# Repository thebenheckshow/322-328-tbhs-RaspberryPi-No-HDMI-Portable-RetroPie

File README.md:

# 322-328-tbhs-RaspberryPi-No-HDMI-Portable-RetroPie
We direct drive a TFT screen with the GPIO of a Rarspberry Pi, connect a GPIO button matrix, install RetroPie, and put it in a sleek portable game form factor.

General overview of steps:

What we did was download and install RetroPie.
Then we connected a TFT screen throught an adapter board from Adafruit.
We used 5 6 5 for the color bit depth. That is 5 bits red 6 bits green and 5 bits blue.
After connecting the screen we made a custom device tree overlay to drive the TFT screen via the GPIO connection.

Using 5 6 5 color bit depth for the TFT screen left us with exactly 8 GPIO for input.
We created a 4x4 button matrix and connected it to the GPIO.
In order to get the operating system to take input from the GPIO button matrix we needed to recompile the kernel with the GPIO button matrix kernel module enabled.
Next we created another device tree overlay to drive the GPIO button matrix.

With all the software and hardware working, Mr. Heckendorn created a sleek enclosure with a nice lasercut faceplace.

Detail of steps:

 - Compile kernel - enable GPIO matrix module

 - Create and compile device tree overlay for GPIO . . .

 - Create and compile device tree overlay for TFT . . .

 - Create a UDEV rule:

   sudo nano /etc/udev/rules.d/10-<name>.rules
   SUBSYSTEM=="input", ATTRS{name}=="<name>", ENV{ID_INPUT_KEYBOARD}="1"

. . .

References:

http://blog.gegg.us/2017/08/a-matrix-keypad-on-a-raspberry-pi-done-right/
https://github.com/adafruit/Adafruit-Retrogame
https://github.com/torvalds/linux/blob/master/include/uapi/linux/input-event-codes.h
https://www.raspberrypi.org/documentation/linux/kernel/building.md

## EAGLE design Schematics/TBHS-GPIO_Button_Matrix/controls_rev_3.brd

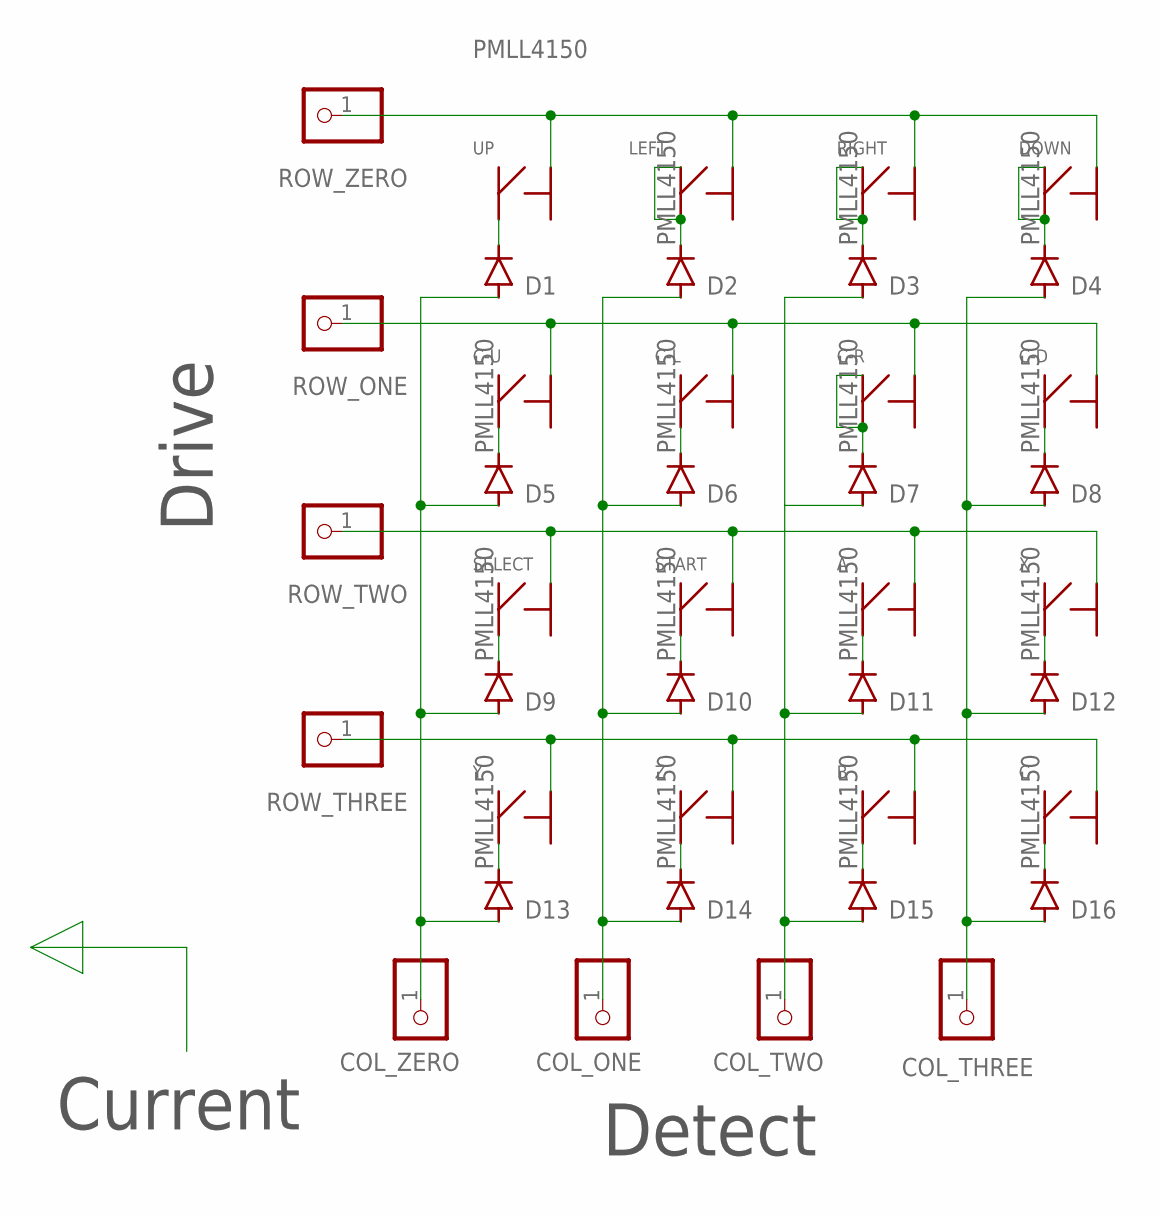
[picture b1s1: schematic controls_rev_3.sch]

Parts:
A: EVQQ2; TACT
B: EVQQ2; TACT
C: EVQQ2; TACT
C-D: EVQQ2; TACT
C-L: EVQQ2; TACT
C-R: EVQQ2; TACT
C-U: EVQQ2; TACT
COL_ONE: PINHD-1X1; 1X01
COL_THREE: PINHD-1X1; 1X01
COL_TWO: PINHD-1X1; 1X01
COL_ZERO: PINHD-1X1; 1X01
D1, D2, D3, D4, D5, D6, D7, D8, D9, D10, D11, D12, D13, D14, D15, D16: PMLL4150; SOD80C
DOWN: EVQQ2; TACT
LEFT: EVQQ2; TACT
RIGHT: EVQQ2; TACT
ROW_ONE: PINHD-1X1; 1X01
ROW_THREE: PINHD-1X1; 1X01
ROW_TWO: PINHD-1X1; 1X01
ROW_ZERO: PINHD-1X1; 1X01
SELECT: EVQQ2; TACT
START: EVQQ2; TACT
UP: EVQQ2; TACT
X: EVQQ2; TACT
Y: EVQQ2; TACT
Z: EVQQ2; TACT

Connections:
1: D1.C, UP.PIN0@0 (PIN0)
COL_ONE: COL_ONE.1, D2.A, D6.A, D10.A, D14.A
COL_THREE: COL_THREE.1, D4.A, D8.A, D12.A, D16.A
COL_TWO: COL_TWO.1, D3.A, D7.A, D11.A, D15.A
COL_ZERO: COL_ZERO.1, D1.A, D5.A, D9.A, D13.A
unnamed: D9.C, SELECT.PIN0@0 (PIN0)
unnamed: C-U.PIN0@0 (PIN0), D5.C
unnamed: D10.C, START.PIN0@0 (PIN0)
unnamed: D12.C, X.PIN0@0 (PIN0)
unnamed: B.PIN0@0 (PIN0), D15.C
unnamed: D14.C, Z.PIN0@0 (PIN0)
unnamed: D13.C, Y.PIN0@0 (PIN0)
unnamed: A.PIN0@0 (PIN0), D11.C
unnamed: C.PIN0@0 (PIN0), D16.C
unnamed: D2.C, LEFT.PIN0@0 (PIN0), LEFT.PIN0@1 (PIN0)
unnamed: D3.C, RIGHT.PIN0@0 (PIN0), RIGHT.PIN0@1 (PIN0)
unnamed: D4.C, DOWN.PIN0@0 (PIN0), DOWN.PIN0@1 (PIN0)
unnamed: C-L.PIN0@0 (PIN0), D6.C
unnamed: C-R.PIN0@0 (PIN0), C-R.PIN0@1 (PIN0), D7.C
unnamed: C-D.PIN0@0 (PIN0), D8.C
ROW_ONE: C-D.PIN1@1 (PIN1), C-L.PIN1@1 (PIN1), C-R.PIN1@1 (PIN1), C-U.PIN1@1 (PIN1), ROW_ONE.1
ROW_THREE: B.PIN1@1 (PIN1), C.PIN1@1 (PIN1), ROW_THREE.1, Y.PIN1@1 (PIN1), Z.PIN1@1 (PIN1)
ROW_TWO: A.PIN1@1 (PIN1), ROW_TWO.1, SELECT.PIN1@1 (PIN1), START.PIN1@1 (PIN1), X.PIN1@1 (PIN1)
ROW_ZERO: DOWN.PIN1@1 (PIN1), LEFT.PIN1@1 (PIN1), RIGHT.PIN1@1 (PIN1), ROW_ZERO.1, UP.PIN1@1 (PIN1)

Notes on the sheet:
Drive
Detect
Current

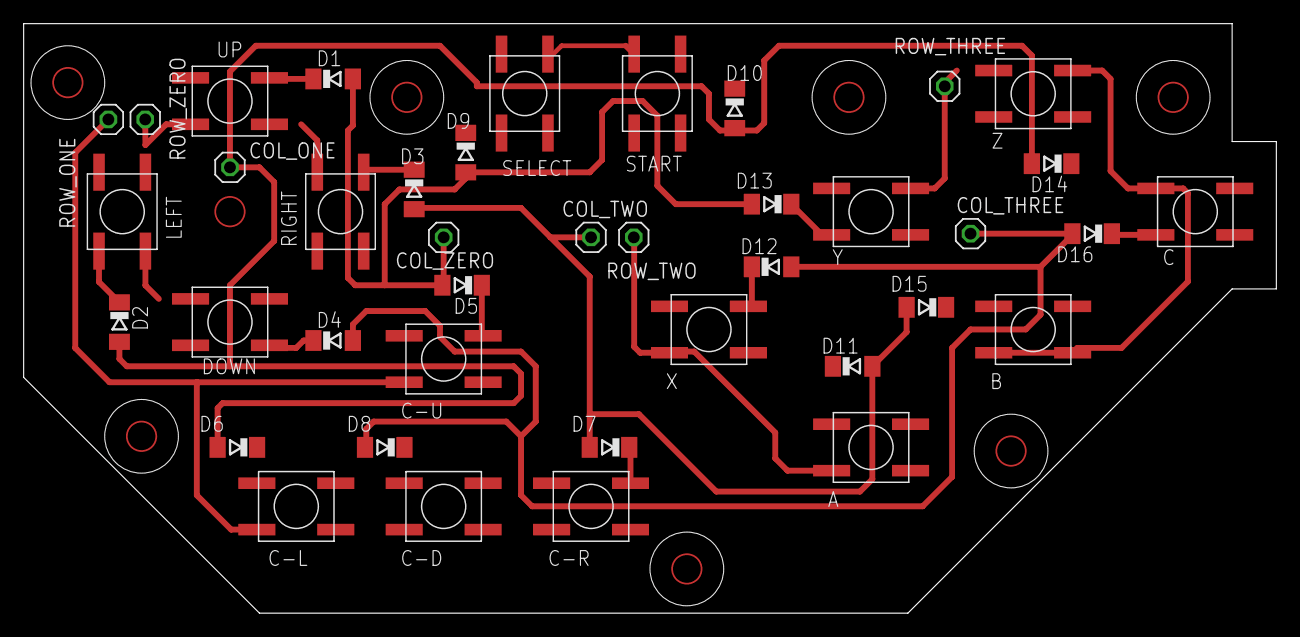
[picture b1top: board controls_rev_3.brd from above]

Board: 2 copper layers, 108.0 x 50.8 mm, 40 parts (0 on the bottom side), 24 nets.

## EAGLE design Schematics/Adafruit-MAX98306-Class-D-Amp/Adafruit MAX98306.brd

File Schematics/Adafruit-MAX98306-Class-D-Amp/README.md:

# Adafruit-MAX98306-Class-D-Amp-PCB
PCB files for the Adafruit MAX98306 Class D Amp

Format is EagleCAD schematic and board layout

For more details, check out the product page at

   * https://www.adafruit.com/product/987

Adafruit invests time and resources providing this open source design, 
please support Adafruit and open-source hardware by purchasing 
products from Adafruit!

Designed by Adafruit Industries.  
Creative Commons Attribution, Share-Alike license, check license.txt for more information
All text above must be included in any redistribution

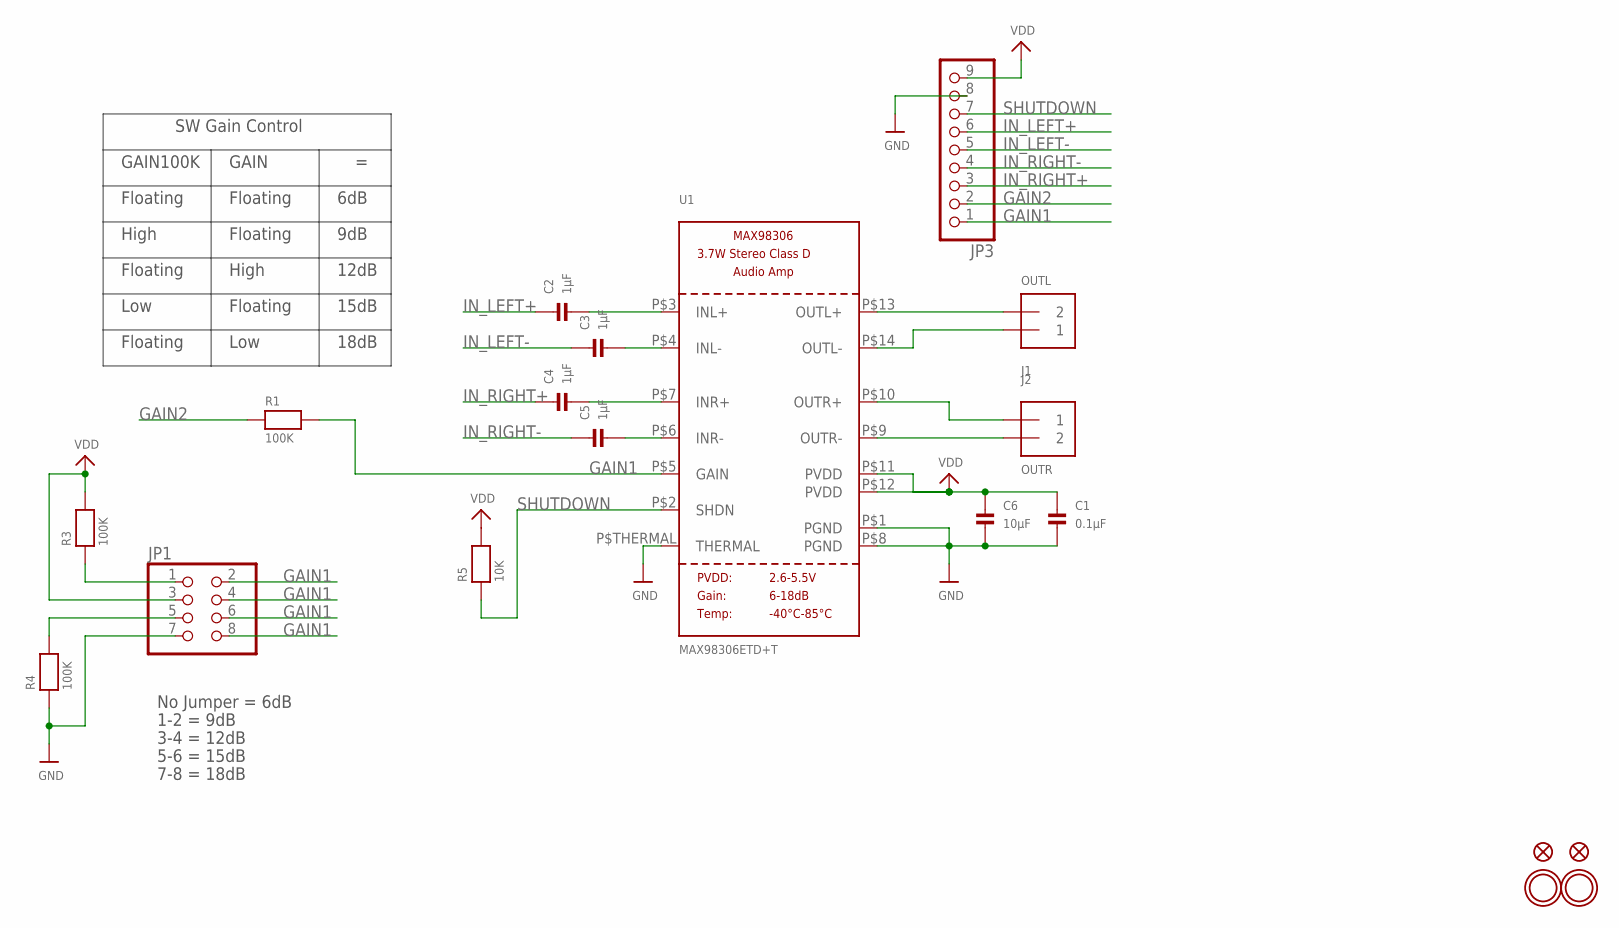
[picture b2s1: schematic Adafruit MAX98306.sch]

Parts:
C1: 0.1µF; 0805
C2, C3, C4, C5: 1µF; 0805
C6: 10µF; 0805
FID1, FID2: FIDUCIAL""; FIDUCIAL_1MM
J1: OUTL; TERMBLOCK_1X2-3.5MM
J2: OUTR; TERMBLOCK_1X2-3.5MM
JP1: PINHD-2X4; 2X04
JP3: HEADER-1X970MIL; 1X09_ROUND_70
R1, R3, R4: 100K; 0805
R5: 10K; 0805
U1: MAX98306ETD+T; TDFN14_3X3MM
U$6, U$7: MOUNTINGHOLE2.5; MOUNTINGHOLE_2.5_PLATED

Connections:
GAIN1: JP1.2, JP1.4, JP1.6, JP1.8, JP3.1, R1.2, U1.P$5 (GAIN)
GAIN2: JP3.2, R1.1
GND: C1.2, C6.2, JP1.7, JP3.8, R4.1, U1.P$1 (PGND), U1.P$8 (PGND), U1.P$THERMAL (THERMAL)
IN_LEFT+: C2.1, JP3.6
IN_LEFT-: C3.1, JP3.5
IN_RIGHT+: C4.1, JP3.3
IN_RIGHT-: C5.1, JP3.4
LOUT-: J1.1, U1.P$14 (OUTL-)
unnamed: JP1.1, R3.1
unnamed: C2.2, U1.P$3 (INL+)
unnamed: JP1.5, R4.2
unnamed: C3.2, U1.P$4 (INL-)
unnamed: C4.2, U1.P$7 (INR+)
unnamed: C5.2, U1.P$6 (INR-)
unnamed: J1.2, U1.P$13 (OUTL+)
unnamed: J2.2, U1.P$9 (OUTR-)
ROUT+: J2.1, U1.P$10 (OUTR+)
SHUTDOWN: JP3.7, R5.1, U1.P$2 (SHDN)
VDD: C1.1, C6.1, JP1.3, JP3.9, R3.2, R5.2, U1.P$11 (PVDD), U1.P$12 (PVDD)

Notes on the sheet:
GAIN100K
GAIN
Floating
6dB
High
9dB
12dB
Low
15dB
18dB
SW Gain Control
No Jumper = 6dB
1-2 = 9dB
3-4 = 12dB
5-6 = 15dB
7-8 = 18dB

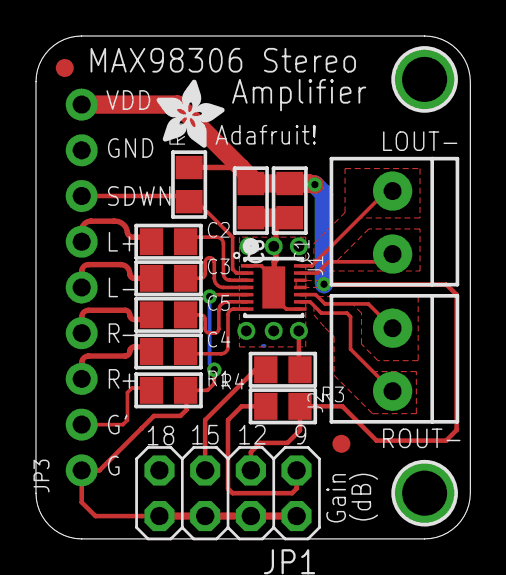
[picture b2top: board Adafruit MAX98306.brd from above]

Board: 2 copper layers, 24.1 x 27.9 mm, 20 parts (0 on the bottom side), 19 nets.

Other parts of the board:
U$10: ADAFRUIT_3.5MM

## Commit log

2018-01-22 Add schematic for A+
2018-01-22 Add schematics
2018-01-22 Add case design files.
2018-01-23 Update bill of materials.
2018-01-24 Update bill of schematic.
2018-01-24 Update schematic.
2018-04-19 Update setup files.
